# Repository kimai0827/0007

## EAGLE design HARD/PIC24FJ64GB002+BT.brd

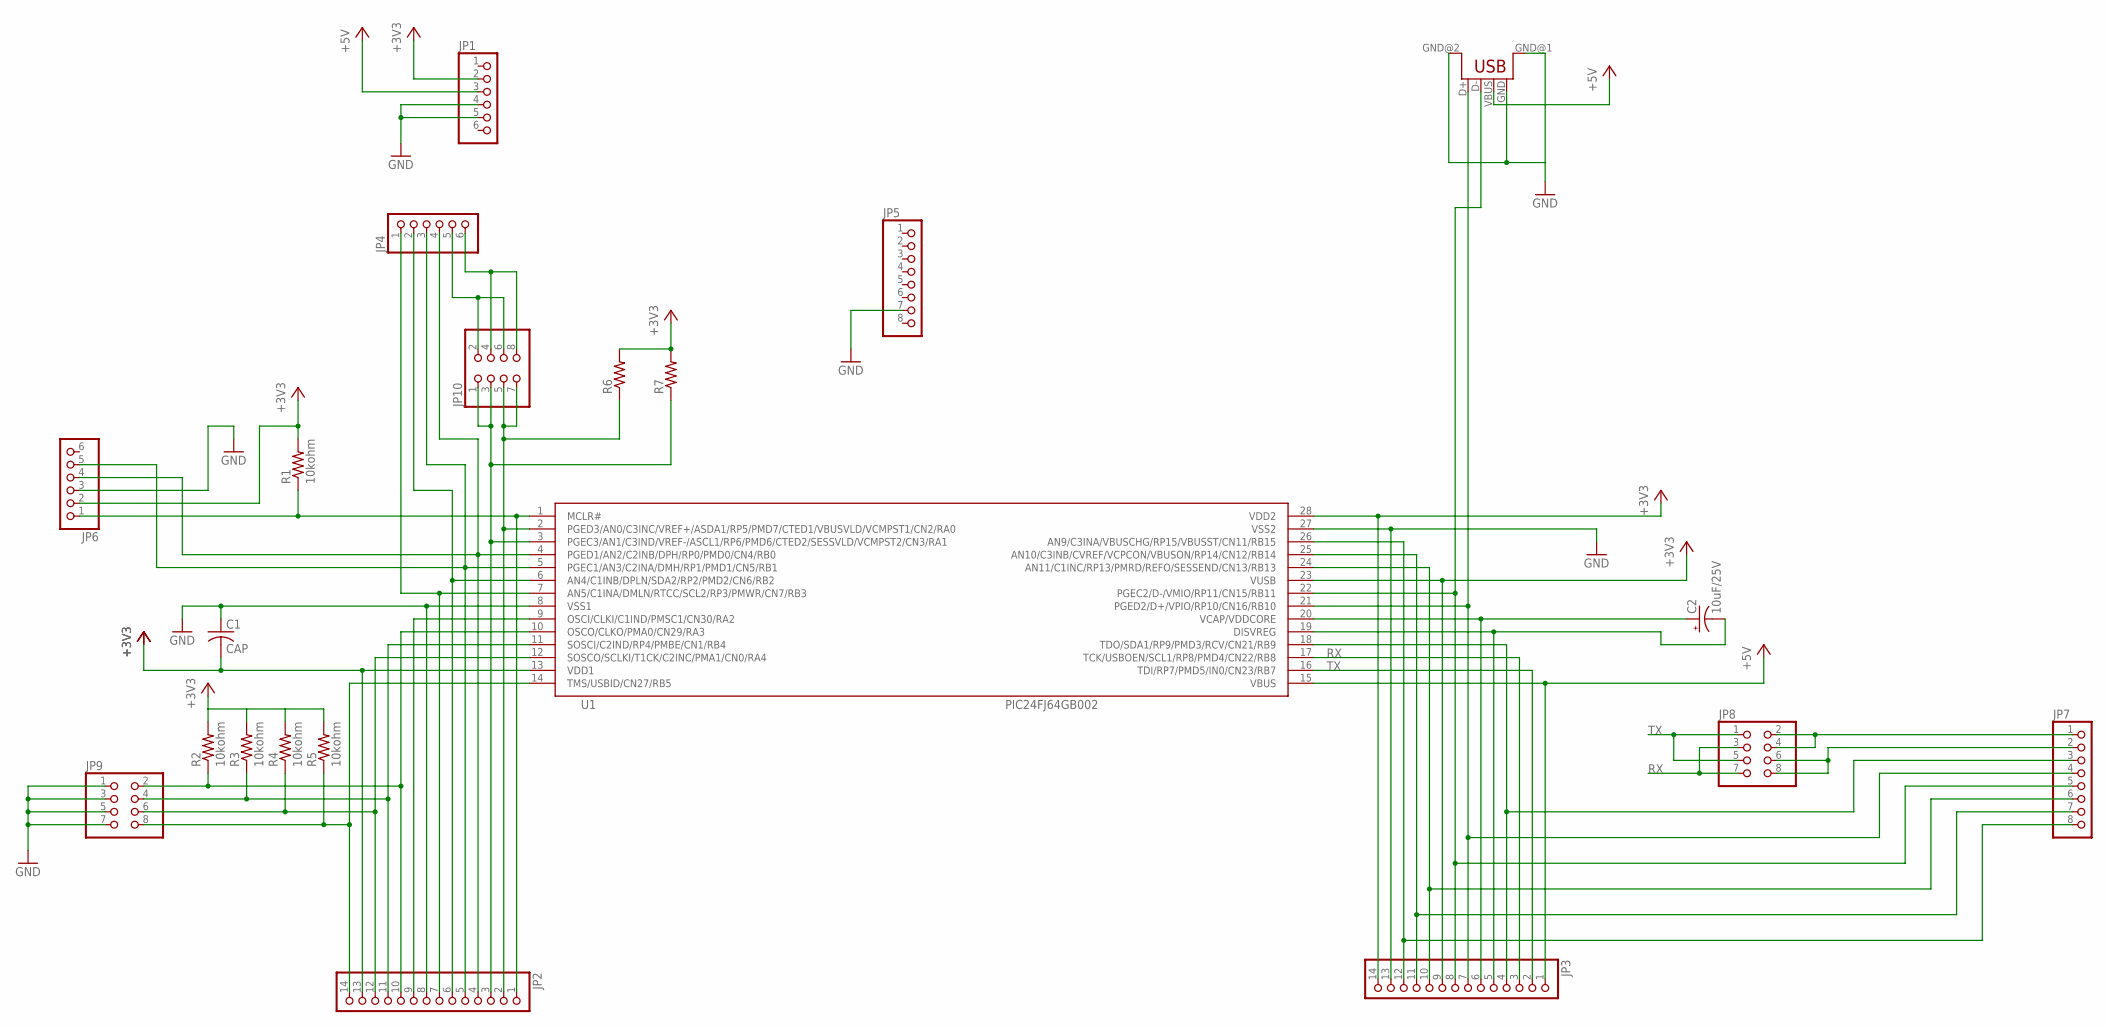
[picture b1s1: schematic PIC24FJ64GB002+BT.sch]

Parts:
C1: CAP; C025-040X050
C2: 10uF/25V; CPOL-US
CON1: USB; USB-FEMALE-A-PTH
JP1, JP4, JP6: PINHD-1X6; 1X06
JP2, JP3: PINHD-1X14; 1X14
JP5, JP7: PINHD-1X8; 1X08
JP8, JP9, JP10: PINHD-2X4; 2X04
R1, R2, R3, R4, R5: 10kohm; 0204V
R6, R7: R-US-01; 0204V
U1: PIC24FJ64GB002; DIP28

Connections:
+3V3: C1.2, JP1.2, JP2.13, JP3.9, JP3.14, JP6.2, R1.2, R2.2, R3.2, R4.2, R5.2, R6.2, R7.2, U1.13 (VDD1), U1.23 (VUSB), U1.28 (VDD2)
+5V: CON1.VBUS, JP1.3, JP3.1, U1.15 (VBUS)
GND: C1.1, CON1.GND, CON1.GND@1 (GND), CON1.GND@2 (GND), JP1.4, JP1.5, JP2.8, JP3.13, JP5.7, JP6.3, JP9.1, JP9.3, JP9.5, JP9.7, U1.8 (VSS1), U1.27 (VSS2)
unnamed: JP2.1, JP6.1, R1.1, U1.1 (MCLR#)
unnamed: C2.+, JP3.6, U1.20 (VCAP/VDDCORE)
unnamed: C2.-, JP3.5, U1.19 (DISVREG)
unnamed: JP2.4, JP4.4, JP6.4, U1.4 (PGED1/AN2/C2INB/DPH/RP0/PMD0/CN4/RB0)
unnamed: JP2.5, JP4.3, JP6.5, U1.5 (PGEC1/AN3/C2INA/DMH/RP1/PMD1/CN5/RB1)
unnamed: JP2.2, JP10.5, JP10.7, R6.1, U1.2 (PGED3/AN0/C3INC/VREF+/ASDA1/RP5/PMD7/CT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)
unnamed: JP2.3, JP10.1, JP10.3, R7.1, U1.3 (PGEC3/AN1/C3IND/VREF-/ASCL1/RP6/PMD6/CT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)
unnamed: JP2.6, JP4.2, U1.6 (AN4/C1INB/DPLN/SDA2/RP2/PMD2/CN6/RB2)
unnamed: JP2.7, JP4.1, U1.7 (AN5/C1INA/DMLN/RTCC/SCL2/RP3/PMWR/CN7/R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)
unnamed: JP2.9, U1.9 (OSCI/CLKI/C1IND/PMSC1/CN30/RA2)
unnamed: JP2.10, JP9.2, R2.1, U1.10 (OSCO/CLKO/PMA0/CN29/RA3)
unnamed: JP2.11, JP9.4, R3.1, U1.11 (SOSCI/C2IND/RP4/PMBE/CN1/RB4)
unnamed: JP2.12, JP9.6, R4.1, U1.12 (SOSCO/SCLKI/T1CK/C2INC/PMA1/CN0/RA4)
unnamed: JP2.14, JP9.8, R5.1, U1.14 (TMS/USBID/CN27/RB5)
unnamed: JP3.11, JP7.7, U1.25 (AN10/C3INB/CVREF/VCPCON/VBUSON/RP14/CN1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)
unnamed: JP3.10, JP7.6, U1.24 (AN11/C1INC/RP13/PMRD/REFO/SESSEND/CN13/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)
unnamed: CON1.D-, JP3.8, JP7.5, U1.22 (PGEC2/D-/VMIO/RP11/CN15/RB11)
unnamed: CON1.D+, JP3.7, JP7.4, U1.21 (PGED2/D+/VPIO/RP10/CN16/RB10)
unnamed: JP3.4, JP7.3, U1.18 (TDO/SDA1/RP9/PMD3/RCV/CN21/RB9)
unnamed: JP4.6, JP10.4, JP10.8
unnamed: JP7.1, JP8.2, JP8.4
unnamed: JP7.2, JP8.6, JP8.8
unnamed: JP4.5, JP10.2, JP10.6
unnamed: JP3.12, JP7.8, U1.26 (AN9/C3INA/VBUSCHG/RP15/VBUSST/CN11/RB15)
RX: JP3.3, JP8.3, JP8.7, U1.17 (TCK/USBOEN/SCL1/RP8/PMD4/CN22/RB8)
TX: JP3.2, JP8.1, JP8.5, U1.16 (TDI/RP7/PMD5/IN0/CN23/RB7)

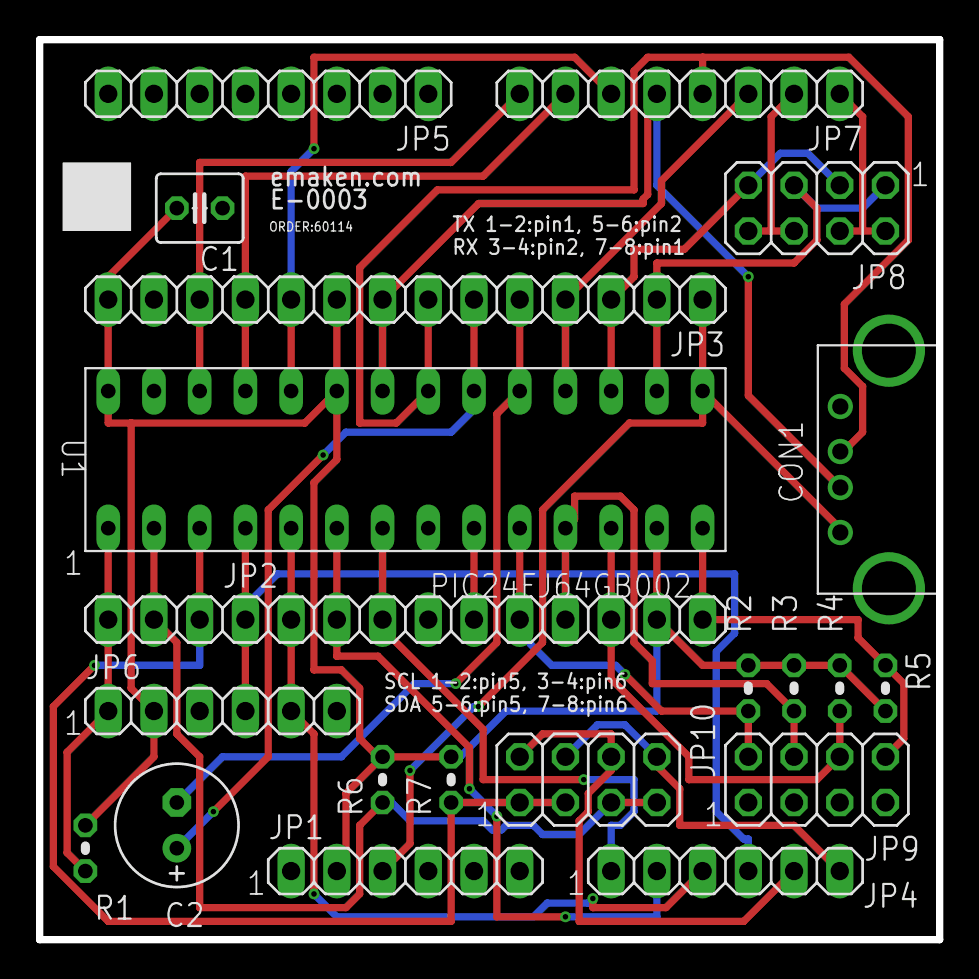
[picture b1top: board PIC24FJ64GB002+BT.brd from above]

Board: 2 copper layers, 50.0 x 50.0 mm, 21 parts (0 on the bottom side), 29 nets.

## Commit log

2012-11-06 initial release
